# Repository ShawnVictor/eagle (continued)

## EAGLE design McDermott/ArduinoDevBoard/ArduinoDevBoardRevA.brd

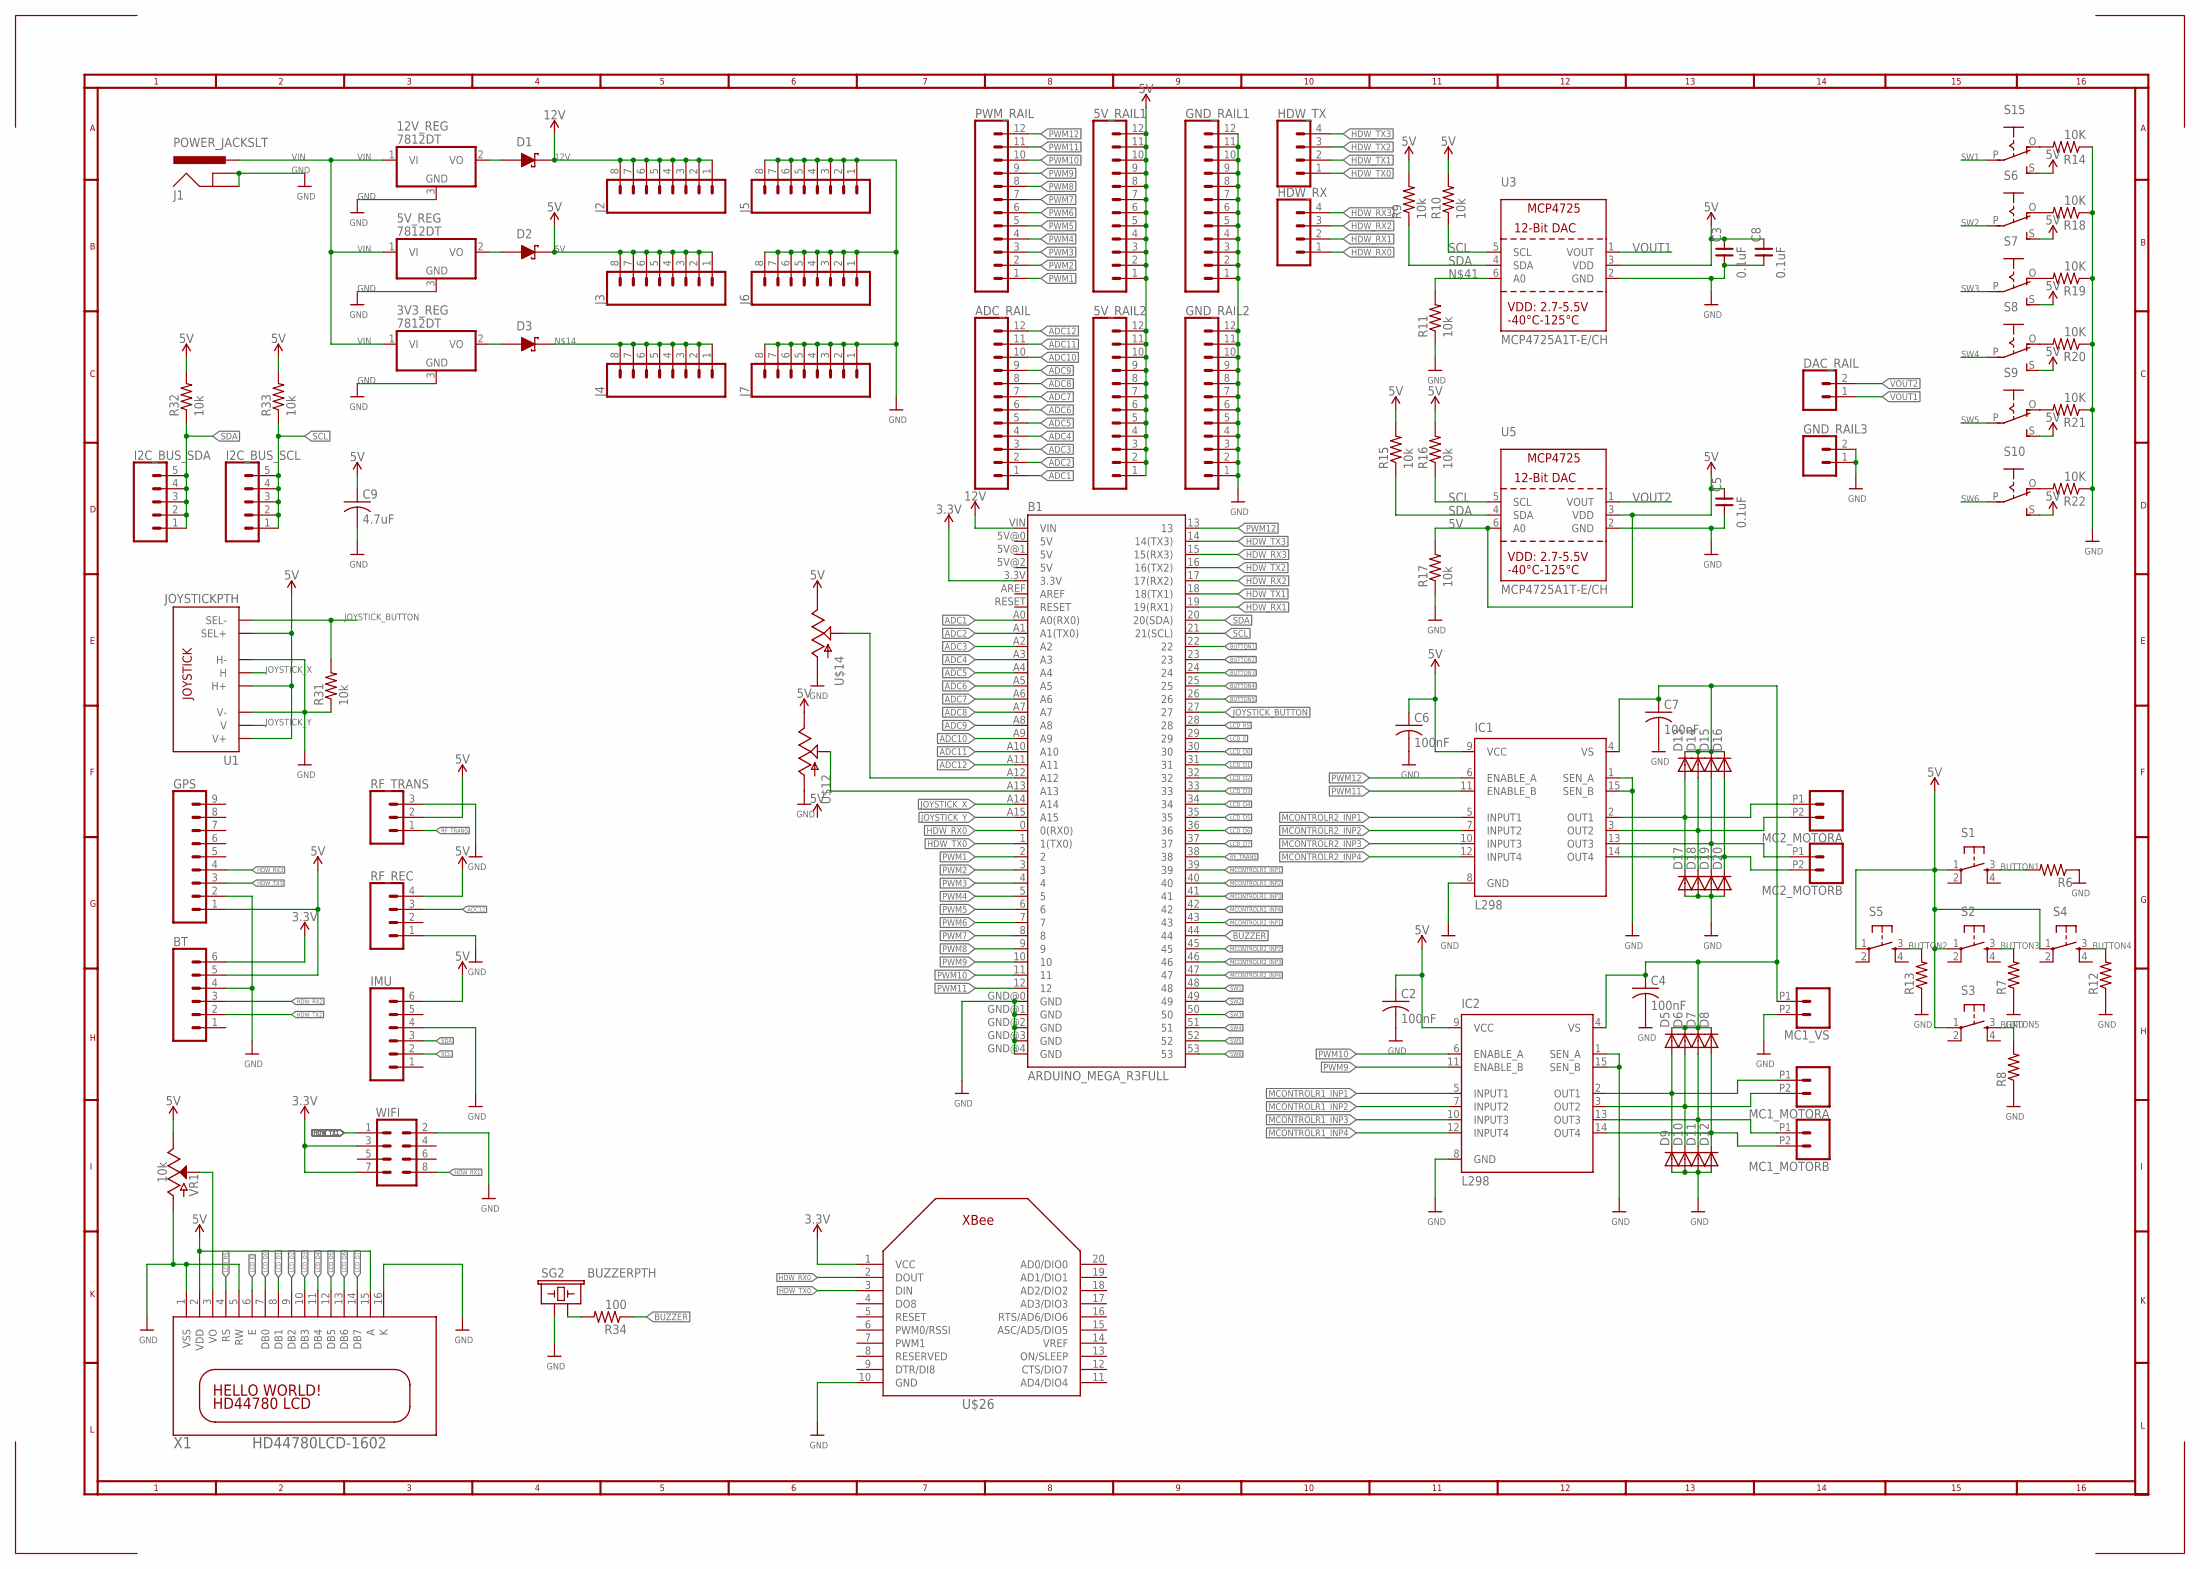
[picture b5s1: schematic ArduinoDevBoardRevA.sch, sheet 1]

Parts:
3V3_REG, 5V_REG, 12V_REG: 7812DT; TO252
5V_RAIL1, 5V_RAIL2: CONN_12; 1X12
ADC_RAIL: CONN_12; 1X12
B1: ARDUINO_MEGA_R3FULL; ARDUINO_MEGA
BT: CONN_06SILK_FEMALE_PTH; 1X06
C2, C4, C6, C7: 100nF; C050-024X044
C3, C5, C8: 0.1uF; 0805
C9: 4.7uF; C050-024X044
D1, D2, D3: D_SCHOTTKYK; SOD-123
D5, D6, D7, D8, D9, D10, D11, D12, D13, D14, D15, D16, D17, D18, D19, D20: DIODE-D-5; D-5
DAC_RAIL: CONN_02; 1X02
GND_RAIL1, GND_RAIL2: CONN_12; 1X12
GND_RAIL3: CONN_02; 1X02
GPS: CONN_09; 1X09
HDW_RX: CONN_04; 1X04
HDW_TX: CONN_04; 1X04
I2C_BUS_SCL, I2C_BUS_SDA: CONN_05; 1X05
IC1, IC2: L298; MULTIWATT-15
IMU: CONN_06SILK_FEMALE_PTH; 1X06
J1: POWER_JACKSLT; POWER_JACK_SLOT
J2, J3, J4, J5, J6, J7: CONN_08"; 1X08
MC1_MOTORA, MC1_MOTORB, MC1_VS, MC2_MOTORA, MC2_MOTORB: CONN_022.54MM_SCREWTERM; 1X02_2.54_SCREWTERM
PWM_RAIL: CONN_12; 1X12
R6, R7, R8, R12, R13: R-US_R0805; R0805
R9, R10, R11, R15, R16, R17, R31, R32, R33: 10k; R0805
R14, R18, R19, R20, R21, R22: 10K; R0805
R34: 100; R0805
RF_REC: CONN_04; 1X04
RF_TRANS: CONN_03; 1X03
S1, S2, S3, S4, S5: TAC_SWITCHSMD; TACTILE_SWITCH_SMD
S6, S7, S8, S9, S10, S15: EG1218S; EG1218
SG2: BUZZERPTH; BUZZER-12MM
U1: JOYSTICKPTH; JOYSTICK
U3, U5: MCP4725A1T-E/CH; SOT23-6
U$12, U$14: POT; ALPS_POT
U$26: XBEE
VR1: 10k; POT-PTH-ALPS-KIT
WIFI: CONN_04X2; 2X4
X1: HD44780LCD-1602; LCD1602

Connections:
3.3V: B1.3.3V, BT.6, U$26.1 (VCC), WIFI.3, WIFI.7
5V: 5V_RAIL1.1, 5V_RAIL1.2, 5V_RAIL1.3, 5V_RAIL1.4, 5V_RAIL1.5, 5V_RAIL1.6, 5V_RAIL1.7, 5V_RAIL1.8, 5V_RAIL1.9, 5V_RAIL1.10, 5V_RAIL1.11, 5V_RAIL1.12, 5V_RAIL2.1, 5V_RAIL2.2, 5V_RAIL2.3, 5V_RAIL2.4, 5V_RAIL2.5, 5V_RAIL2.6, 5V_RAIL2.7, 5V_RAIL2.8, 5V_RAIL2.9, 5V_RAIL2.10, 5V_RAIL2.11, 5V_RAIL2.12, BT.5, C2.1, C3.2, C5.2, C6.1, C8.2, C9.1, D2.2 (C), GPS.1, IC1.9 (VCC), IC2.9 (VCC), IMU.6, J3.1, J3.2, J3.3, J3.4, J3.5, J3.6, J3.7, J3.8, R9.2, R10.2, R15.2, R16.2, R17.2, R32.2, R33.2, RF_REC.4, RF_TRANS.2, S1.1, S2.1, S3.1, S4.1, S5.1, S6.S, S7.S, S8.S, S9.S, S10.S, S15.S, U1.B1A (SEL+), U1.H1 (H+), U1.V1 (V+), U3.3 (VDD), U5.3 (VDD), U5.6 (A0), U$12.P$1 (E), U$14.P$1 (E), VR1.P$1 (E), X1.2 (VDD), X1.15 (A); also elsewhere on the board
12V: B1.VIN, D1.2 (C), J2.1, J2.2, J2.3, J2.4, J2.5, J2.6, J2.7, J2.8
ADC1: ADC_RAIL.1, B1.A0 (A0(RX0)); also elsewhere on the board
ADC2: ADC_RAIL.2, B1.A1 (A1(TX0)); also elsewhere on the board
ADC3: ADC_RAIL.3, B1.A2; also elsewhere on the board
ADC4: ADC_RAIL.4, B1.A3
ADC5: ADC_RAIL.5, B1.A4
ADC6: ADC_RAIL.6, B1.A5
ADC7: ADC_RAIL.7, B1.A6
ADC8: ADC_RAIL.8, B1.A7
ADC9: ADC_RAIL.9, B1.A8
ADC10: ADC_RAIL.10, B1.A9
ADC11: ADC_RAIL.11, B1.A10
ADC12: ADC_RAIL.12, B1.A11, RF_REC.3
BUTTON1: B1.22, R6.2, S1.3
BUTTON2: B1.23, R13.2, S5.3
BUTTON3: B1.24, R7.2, S2.3
BUTTON4: B1.25, R12.2, S4.3
BUTTON5: B1.26, R8.2, S3.3
BUZZER: B1.44, R34.1
GND: 3V3_REG.3 (GND), 5V_REG.3 (GND), 12V_REG.3 (GND), B1.GND@0 (GND), B1.GND@1 (GND), B1.GND@2 (GND), B1.GND@3 (GND), B1.GND@4 (GND), BT.4, C2.2, C3.1, C4.2, C5.1, C6.2, C7.2, C8.1, C9.2, D9.A, D10.A, D11.A, D12.A, D17.A, D18.A, D19.A, D20.A, GND_RAIL1.1, GND_RAIL1.2, GND_RAIL1.3, GND_RAIL1.4, GND_RAIL1.5, GND_RAIL1.6, GND_RAIL1.7, GND_RAIL1.8, GND_RAIL1.9, GND_RAIL1.10, GND_RAIL1.11, GND_RAIL1.12, GND_RAIL2.1, GND_RAIL2.2, GND_RAIL2.3, GND_RAIL2.4, GND_RAIL2.5, GND_RAIL2.6, GND_RAIL2.7, GND_RAIL2.8, GND_RAIL2.9, GND_RAIL2.10, GND_RAIL2.11, GND_RAIL2.12, GND_RAIL3.1, GND_RAIL3.2, GPS.2, IC1.1 (SEN_A), IC1.8 (GND), IC1.15 (SEN_B), IC2.1 (SEN_A), IC2.8 (GND), IC2.15 (SEN_B), IMU.4, J1.GND@1 (GNDBREAK), J1.GND@2 (GND), J5.1, J5.2, J5.3, J5.4, J5.5, J5.6, J5.7, J5.8, J6.1, J6.2, J6.3, J6.4, J6.5, J6.6, J6.7, J6.8, J7.1, J7.2, J7.3, J7.4, J7.5, J7.6, J7.7, J7.8, MC1_VS.P2 (2), R6.1, R7.1, R8.1, R11.1, R12.1, R13.1, R14.1, R17.1, R18.1, R19.1, R20.1, R21.1, R22.1, R31.1, RF_REC.1, RF_TRANS.3, SG2.+ (1), U1.H3 (H-), U1.V3 (V-), U3.2 (GND), U5.2 (GND), U$12.P$3 (A), U$14.P$3 (A), U$26.10 (GND), VR1.P$3 (A), WIFI.2, X1.1 (VSS), X1.5 (RW), X1.16 (K); also elsewhere on the board
HDW_RX0: B1.0 (0(RX0)), HDW_RX.1, U$26.2 (DOUT)
HDW_RX1: B1.19 (19(RX1)), HDW_RX.2, WIFI.8
HDW_RX2: B1.17 (17(RX2)), BT.3, HDW_RX.3
HDW_RX3: B1.15 (15(RX3)), GPS.4, HDW_RX.4
HDW_TX0: B1.1 (1(TX0)), HDW_TX.1, U$26.3 (DIN)
HDW_TX1: B1.18 (18(TX1)), HDW_TX.2, WIFI.1
HDW_TX2: B1.16 (16(TX2)), BT.2, HDW_TX.3
HDW_TX3: B1.14 (14(TX3)), GPS.3, HDW_TX.4
JOYSTICK_BUTTON: B1.27, R31.2, U1.B2A (SEL-)
JOYSTICK_X: B1.A14, U1.H2 (H)
JOYSTICK_Y: B1.A15, U1.V2 (V)
LCD_D0: B1.30, X1.7 (DB0)
LCD_D1: B1.31, X1.8 (DB1)
LCD_D2: B1.32, X1.9 (DB2)
LCD_D3: B1.33, X1.10 (DB3)
LCD_D4: B1.34, X1.11 (DB4)
LCD_D5: B1.35, X1.12 (DB5)
LCD_D6: B1.36, X1.13 (DB6)
LCD_D7: B1.37, X1.14 (DB7)
LCD_E: B1.29, X1.6 (E)
LCD_RS: B1.28, X1.4 (RS)
MCONTROLR1_INP1: B1.39, IC2.5 (INPUT1)
MCONTROLR1_INP2: B1.40, IC2.7 (INPUT2)
MCONTROLR1_INP3: B1.41, IC2.10 (INPUT3)
MCONTROLR1_INP4: B1.42, IC2.12 (INPUT4)
MCONTROLR2_INP1: B1.43, IC1.5 (INPUT1)
MCONTROLR2_INP2: B1.45, IC1.7 (INPUT2)
MCONTROLR2_INP3: B1.46, IC1.10 (INPUT3)
MCONTROLR2_INP4: B1.47, IC1.12 (INPUT4)
unnamed: 12V_REG.2 (VO), D1.1 (A)
unnamed: 5V_REG.2 (VO), D2.1 (A)
unnamed: 3V3_REG.2 (VO), D3.1 (A)
unnamed: C4.1, C7.1, D5.C, D6.C, D7.C, D8.C, D13.C, D14.C, D15.C, D16.C, IC1.4 (VS), IC2.4 (VS), MC1_VS.P1 (1)
unnamed: D3.2 (C), J4.1, J4.2, J4.3, J4.4, J4.5, J4.6, J4.7, J4.8
unnamed: D13.A, D17.C, IC1.2 (OUT1), MC2_MOTORA.P1 (1)
unnamed: D14.A, D18.C, IC1.3 (OUT2), MC2_MOTORA.P2 (2)
unnamed: D15.A, D19.C, IC1.13 (OUT3), MC2_MOTORB.P1 (1)
unnamed: D16.A, D20.C, IC1.14 (OUT4), MC2_MOTORB.P2 (2)
unnamed: B1.A12, U$14.P$2 (S)
unnamed: B1.A13, U$12.P$2 (S)
unnamed: VR1.P$2 (S), X1.3 (VO)
unnamed: R34.2, SG2.- (2)
unnamed: R11.2, U3.6 (A0)
unnamed: D5.A, D9.C, IC2.2 (OUT1), MC1_MOTORA.P1 (1)
unnamed: D6.A, D10.C, IC2.3 (OUT2), MC1_MOTORA.P2 (2)
unnamed: D7.A, D11.C, IC2.13 (OUT3), MC1_MOTORB.P1 (1)
unnamed: D8.A, D12.C, IC2.14 (OUT4), MC1_MOTORB.P2 (2)
unnamed: R14.2, S15.O
unnamed: R18.2, S6.O
unnamed: R19.2, S7.O
unnamed: R20.2, S8.O
unnamed: R21.2, S9.O
unnamed: R22.2, S10.O
PWM1: B1.2, PWM_RAIL.1
PWM2: B1.3, PWM_RAIL.2
PWM3: B1.4, PWM_RAIL.3
PWM4: B1.5, PWM_RAIL.4
PWM5: B1.6, PWM_RAIL.5
PWM6: B1.7, PWM_RAIL.6
PWM7: B1.8, PWM_RAIL.7
PWM8: B1.9, PWM_RAIL.8
PWM9: B1.10, IC2.11 (ENABLE_B), PWM_RAIL.9
PWM10: B1.11, IC2.6 (ENABLE_A), PWM_RAIL.10
PWM11: B1.12, IC1.11 (ENABLE_B), PWM_RAIL.11
PWM12: B1.13, IC1.6 (ENABLE_A), PWM_RAIL.12
RF_TRANS: B1.38, RF_TRANS.1
SCL: B1.21 (21(SCL)), I2C_BUS_SCL.1, I2C_BUS_SCL.2, I2C_BUS_SCL.3, I2C_BUS_SCL.4, I2C_BUS_SCL.5, IMU.2, R10.1, R16.1, R33.1, U3.5 (SCL), U5.5 (SCL); also elsewhere on the board
SDA: B1.20 (20(SDA)), I2C_BUS_SDA.1, I2C_BUS_SDA.2, I2C_BUS_SDA.3, I2C_BUS_SDA.4, I2C_BUS_SDA.5, IMU.3, R9.1, R15.1, R32.1, U3.4 (SDA), U5.4 (SDA); also elsewhere on the board
SW1: B1.48, S15.P
SW2: B1.49, S6.P
SW3: B1.50, S7.P
SW4: B1.51, S8.P
SW5: B1.52, S9.P
SW6: B1.53, S10.P
VIN: 3V3_REG.1 (VI), 5V_REG.1 (VI), 12V_REG.1 (VI), J1.PWR
VOUT1: DAC_RAIL.1, U3.1 (VOUT)
VOUT2: DAC_RAIL.2, U5.1 (VOUT)

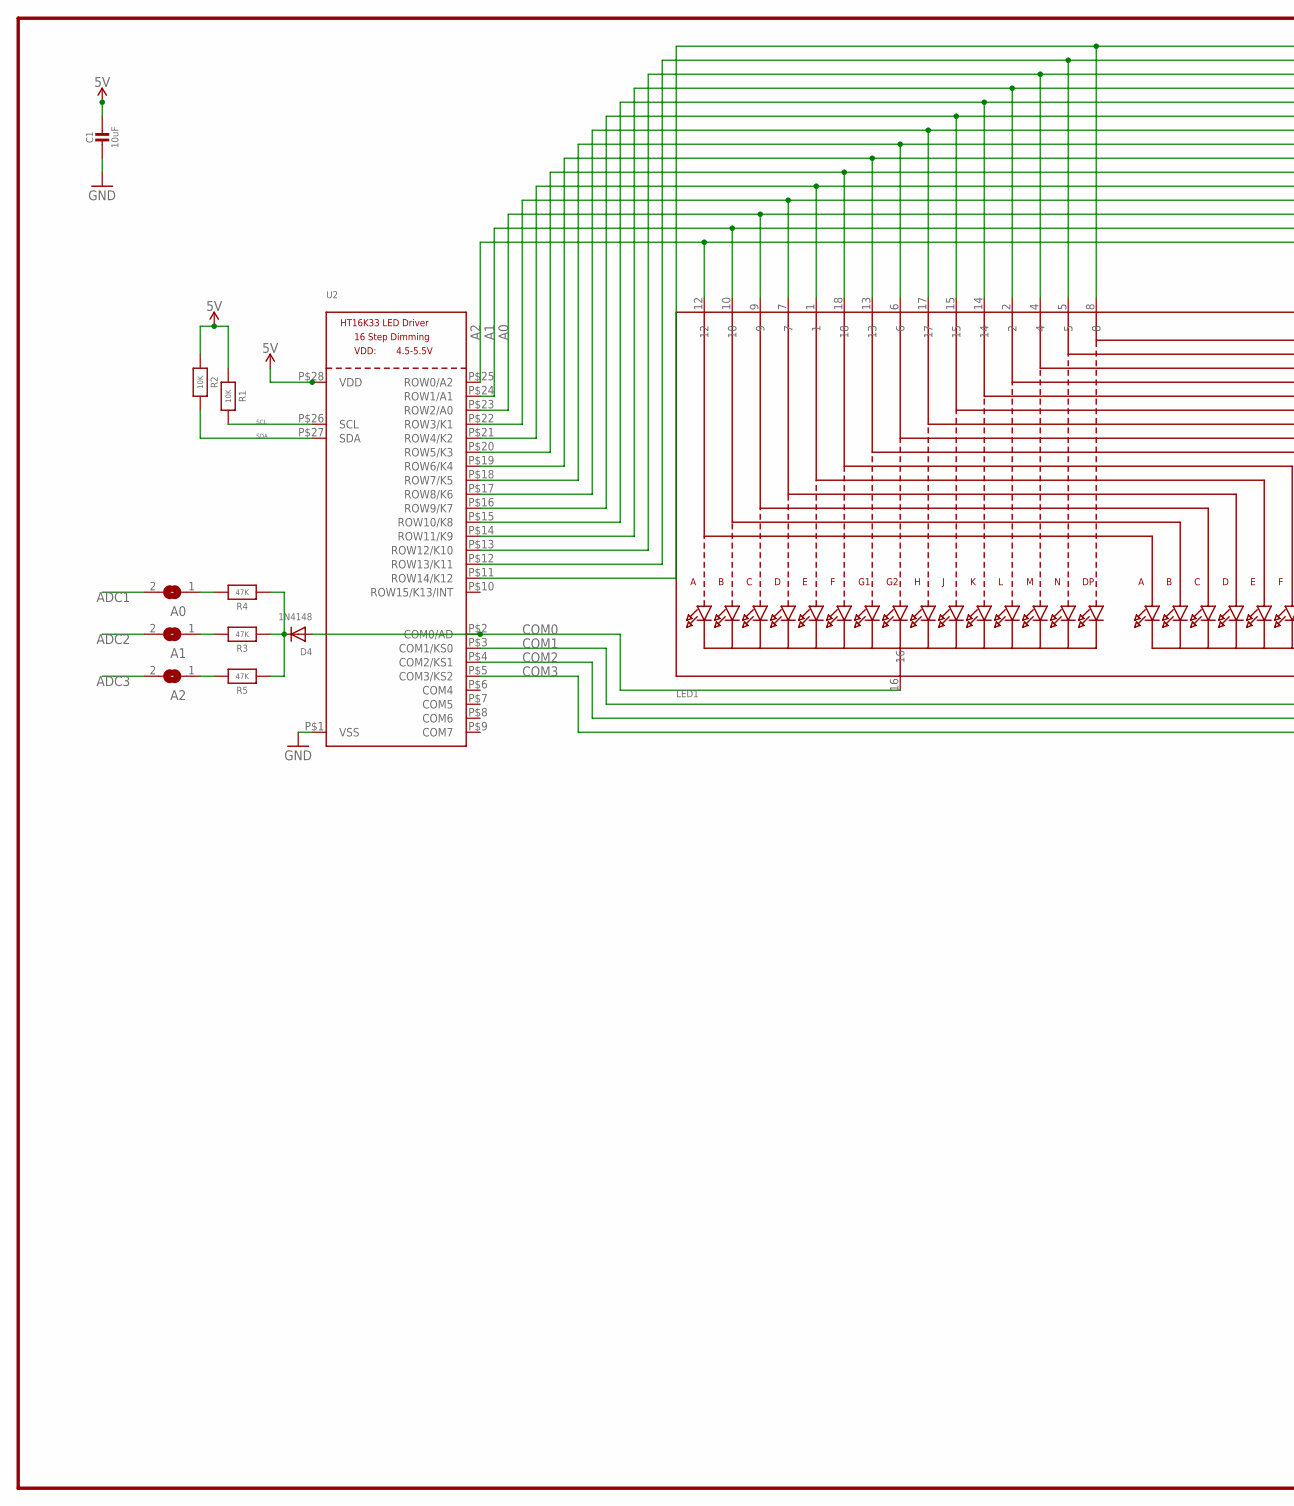
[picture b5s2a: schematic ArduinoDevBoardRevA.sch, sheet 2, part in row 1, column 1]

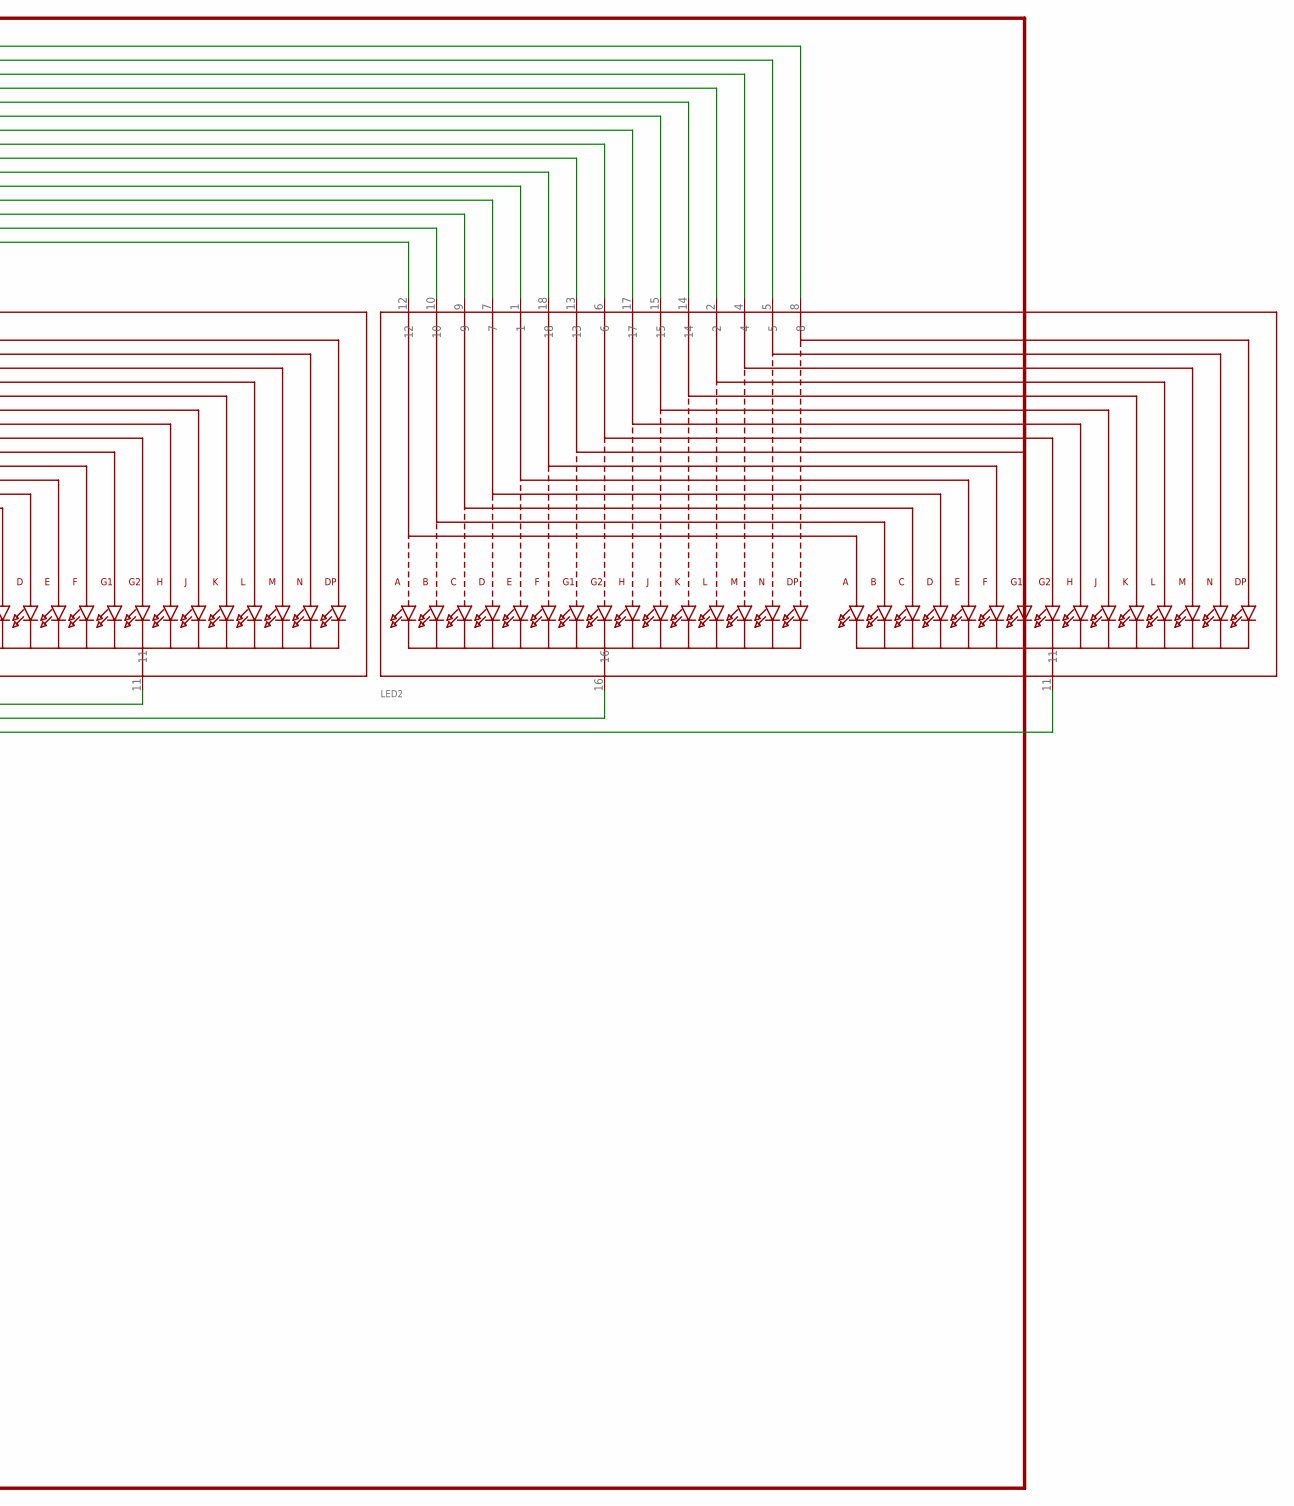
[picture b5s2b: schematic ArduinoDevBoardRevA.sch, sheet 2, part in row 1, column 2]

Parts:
A0, A1, A2: SOLDERJUMPERREFLOW_NOPASTE; SOLDERJUMPER_REFLOW_NOPASTE
C1: 10uF; 0805-NO
D4: 1N4148; SOD-323F
LED1, LED2: DISP_SEGMENT_STARBURST_DUAL_COMMONCATHODE; SEGMENT_STARTBUST_DUAL_KWA-541CBB
R1, R2: 10K; 0805-NO
R3, R4, R5: 47K; 0805-NO
U2: HT16K33_SOP28; SOP28_300MIL

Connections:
5V: R1.1, R2.1, U2.P$28 (VDD); also elsewhere on the board
A0: LED1.9, LED2.9, U2.P$23 (ROW2/A0)
A1: LED1.10, LED2.10, U2.P$24 (ROW1/A1)
A2: LED1.12, LED2.12, U2.P$25 (ROW0/A2)
ADC1: A0.2; also elsewhere on the board
ADC2: A1.2; also elsewhere on the board
ADC3: A2.2; also elsewhere on the board
COM0: D4.A, LED1.16, U2.P$2 (COM0/AD)
COM1: LED1.11, U2.P$3 (COM1/KS0)
COM2: LED2.16, U2.P$4 (COM2/KS1)
COM3: LED2.11, U2.P$5 (COM3/KS2)
GND: C1.2, U2.P$1 (VSS); also elsewhere on the board
unnamed: LED1.7, LED2.7, U2.P$22 (ROW3/K1)
unnamed: LED1.1, LED2.1, U2.P$21 (ROW4/K2)
unnamed: LED1.18, LED2.18, U2.P$20 (ROW5/K3)
unnamed: A1.1, R3.2
unnamed: A0.1, R4.2
unnamed: LED1.13, LED2.13, U2.P$19 (ROW6/K4)
unnamed: LED1.6, LED2.6, U2.P$18 (ROW7/K5)
unnamed: D4.C, R3.1, R4.1, R5.1
unnamed: A2.1, R5.2
unnamed: LED1.17, LED2.17, U2.P$17 (ROW8/K6)
unnamed: LED1.15, LED2.15, U2.P$16 (ROW9/K7)
unnamed: LED1.14, LED2.14, U2.P$15 (ROW10/K8)
unnamed: LED1.2, LED2.2, U2.P$14 (ROW11/K9)
unnamed: LED1.4, LED2.4, U2.P$13 (ROW12/K10)
unnamed: LED1.5, LED2.5, U2.P$12 (ROW13/K11)
unnamed: LED1.8, LED2.8, U2.P$11 (ROW14/K12)
SCL: R1.2, U2.P$26 (SCL); also elsewhere on the board
SDA: R2.2, U2.P$27 (SDA); also elsewhere on the board

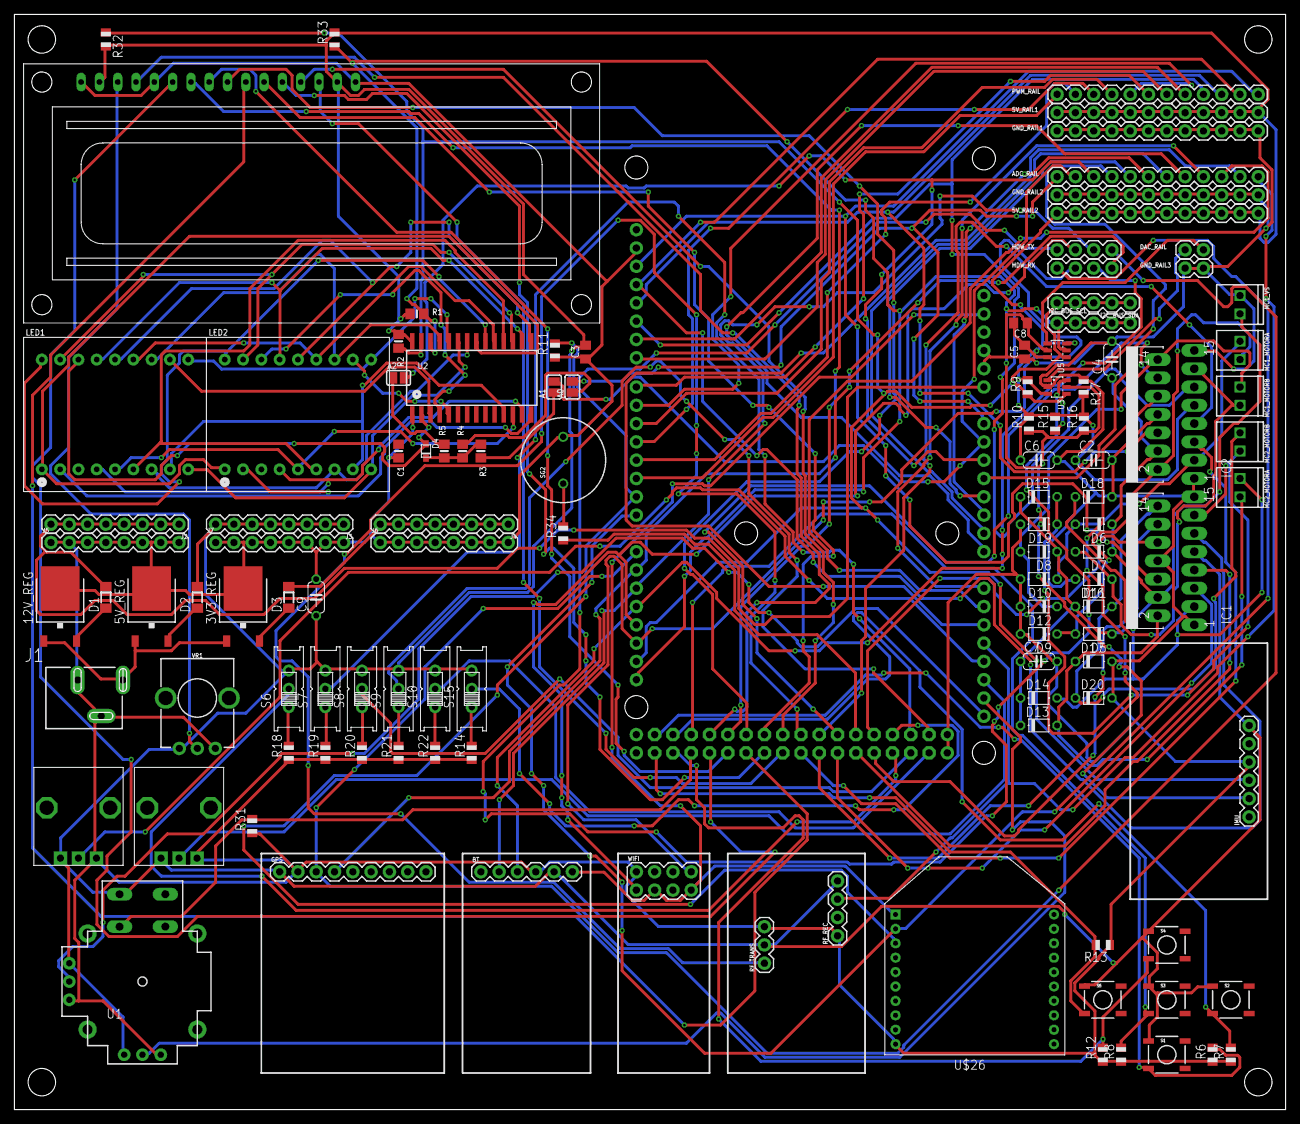
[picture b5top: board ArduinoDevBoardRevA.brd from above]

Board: 2 copper layers, 176.5 x 152.1 mm, 117 parts (1 on the bottom side), 122 nets.

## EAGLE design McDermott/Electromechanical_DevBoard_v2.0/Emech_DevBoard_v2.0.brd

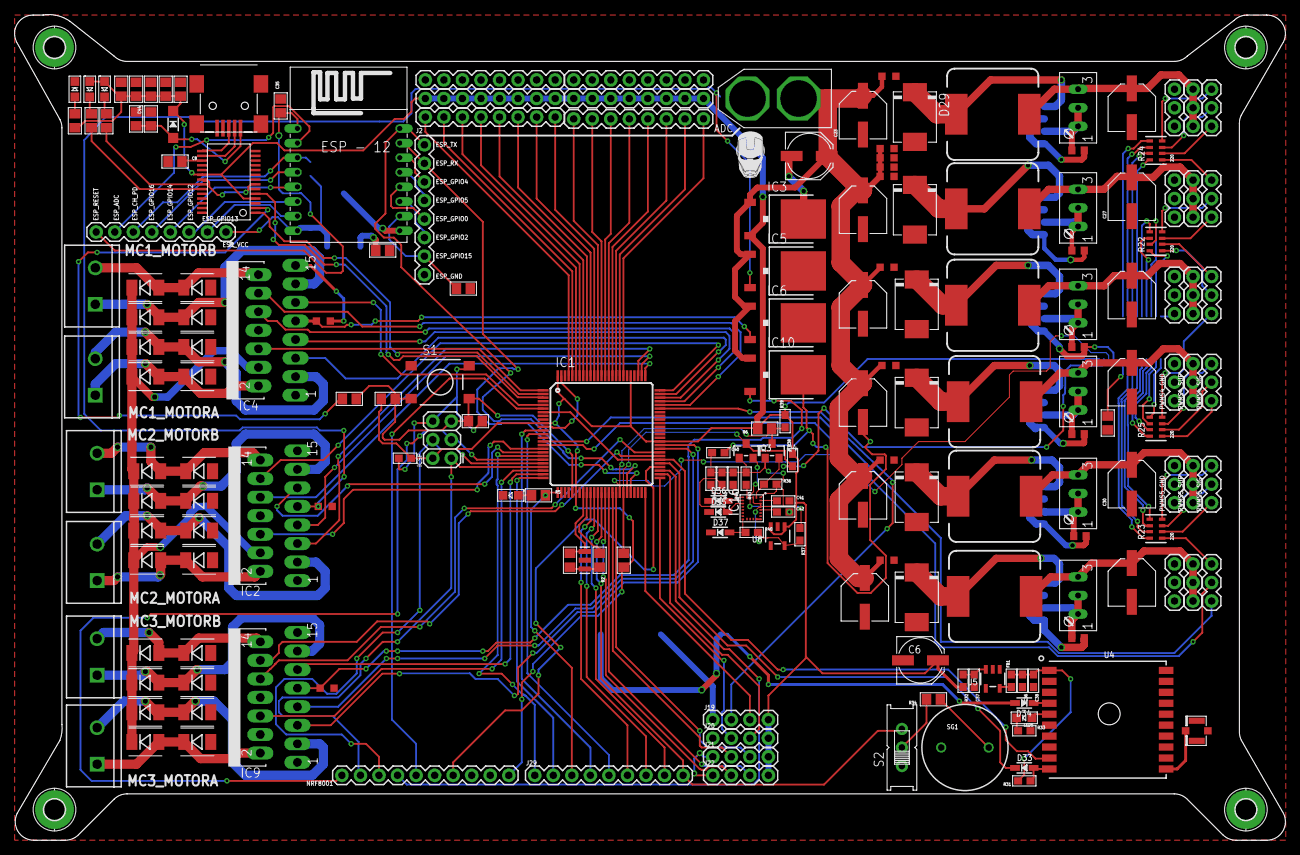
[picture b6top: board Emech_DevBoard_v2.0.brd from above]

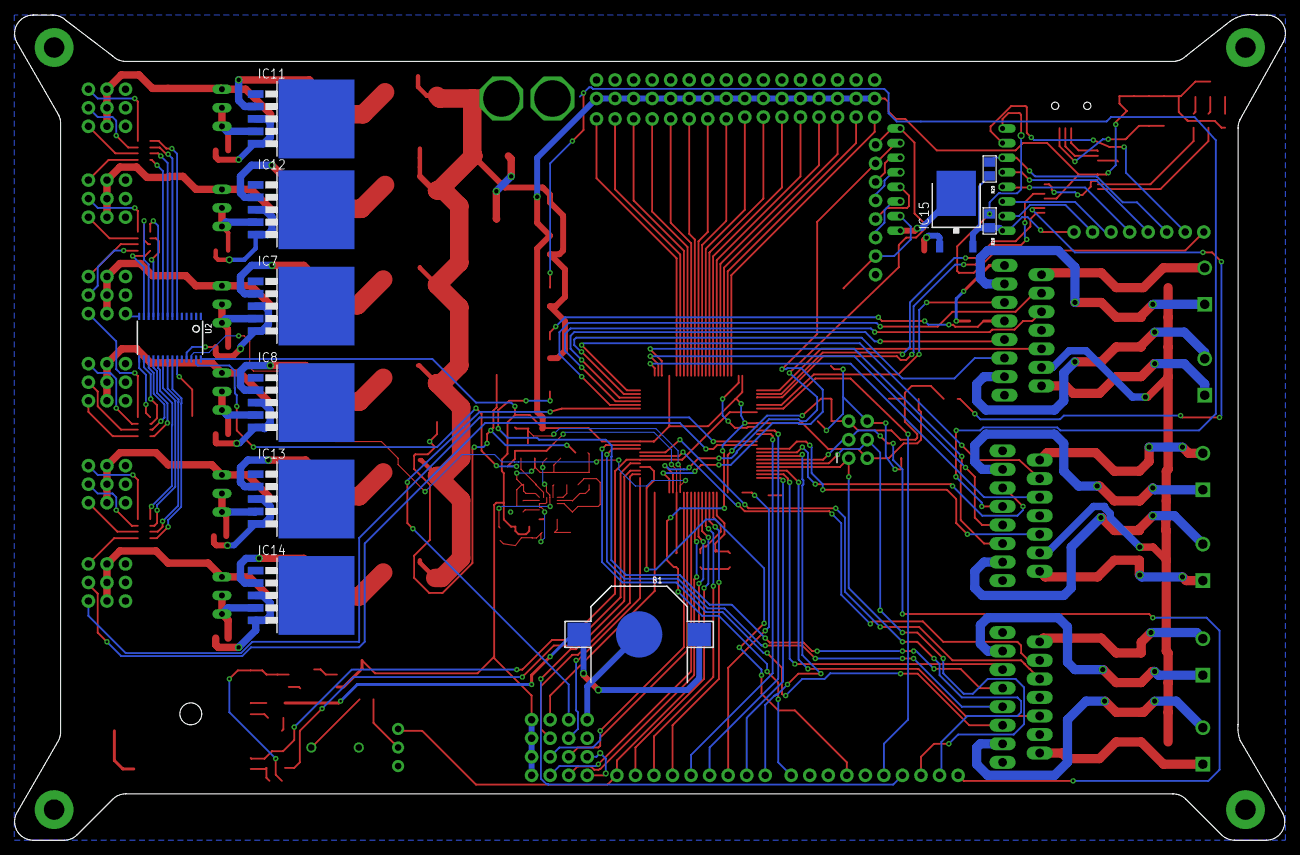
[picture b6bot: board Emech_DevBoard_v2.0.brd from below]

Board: 2 copper layers, 174.1 x 113.1 mm, 210 parts (11 on the bottom side), 185 nets.

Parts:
B1: CR1220
C1, C2, C3, C4, C7, C8, C10, C35, C44: 0.1uF; 0805
C5, C6: 47uF; PANASONIC_D
C9: 4.7uF; 0805
C11, C12, C13, C15, C18, C22: 0.1uF; 0603
C14, C16, C19, C20, C23, C24, C26, C27, C29, C30, C32, C33: 220uF@35V; PANASONIC_D
C17, C21, C25, C28, C31, C34: 100nF; 0603
C36, C37, C39, C40: 10µF; 0603
C38: 0.1µF; 0603
C41: 0.22uF; 0603
C42: 10uF; 0603
C43: 0.33uF; 0805
CN2: USB-MINIB
D2: SOD-123
D3, D4, D5, D6, D7, D8, D9, D10, D11, D12, D13, D14, D15, D16, D17, D18, D21, D22, D23, D24, D25, D26, D27, D28: SS24FSCT-ND; DO-214AA
D19, D20, D29, D30, D31, D32: SS54; DO214AB
D33, D35, D36, D37: 1N4148; SOD-323
D34: CUS520; SOD-323
FB1: 0603
H1, H2, H3, H4: MOUNT-PAD-ROUND2.8; 2,8-PAD
IC1: ATMEGA2560; TQFP100
IC2, IC4, IC9: L298; MULTIWATT-15
IC3: UA78M05; TO252
IC5, IC6, IC10, IC15: 7806DT; TO252
IC7, IC8, IC11, IC12, IC13, IC14: LM2596S; TO263-5
IC16: LSM9DS1; LGA24_3.5X3.1MM
ICSP: FEMALE 2x3; 2X3
J1, J2, J23, J24, J25, J26, J27, J28: 1X08
J19, J20, J21, J22: 1X04
J29: 1X09
L1, L2, L3, L4, L5, L6: SRR1280-330mH; SRR1280
LED1: GREEN; CHIPLED_0805
LED2: YELLOW; CHIPLED_0805
LED3: BLUE; CHIPLED_0805
LED4, LED5: RED; CHIPLED_0805
MC1_MOTORA, MC1_MOTORB, MC2_MOTORA, MC2_MOTORB, MC3_MOTORA, MC3_MOTORB: SCREWTERMINAL-5MM-2
NRF8001: 1X10
PWMS1_GND, PWMS1_SIG, PWMS1_SUP, PWMS2_GND, PWMS2_SIG, PWMS2_SUP, PWMS3_GND, PWMS3_SIG, PWMS3_SUP, PWMS4_GND, PWMS4_SIG, PWMS4_SUP, PWMS5_GND, PWMS5_SIG, PWMS5_SUP, PWMS6_GND, PWMS6_SIG, PWMS6_SUP: 1X03
Q3, Q4: BSS138; SOT23-WIDE
R1: 1m; 0805
R2: 27; 0805
R3, R6, R7, R26, R27, R28: 10k; 0805
R4, R5, R29, R30: 1k; 0805
R8, R9: 680; 0805
R10, R12, R14, R16, R18, R20: 10k; S64W
R11, R13, R15, R17, R19, R21: 330; R0603
R22, R23, R24, R25: 220; RESPACK_4X0603
R31, R32: 10k; 0603
R33: 1k; 0603
R34: 100; 0805
R36, R37, R38, R39, R40, R41, R42, R43, R44: 10K; 0603
S1: DTSM-6
S2: EG1218
SG1: BUZZERPTH; BUZZER-12MM
U1: SSOP28DB
U2: PCA9685; TSSOP28
U3: ESP12
U4: FGPMMOPA6H
U5, U8: MIC5225-3.3; SOT23-5
U$1: RESONATORSMD; RESONATOR-SMD
U$14: XT60
U$55: U.FL

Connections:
3.3V: C8.2, U1.17
ADC0: IC1.97, J25.8
ADC1: IC1.96, J25.7
ADC2: IC1.95, J25.6
ADC3: IC1.94, J25.5
ADC4: IC1.93, J25.4
ADC5: IC1.92, J25.3
ADC6: IC1.91, J25.2
ADC7: IC1.90, J25.1
ADC8: IC1.89, J28.8
ADC9: IC1.88, J28.7
ADC10: IC1.87, J28.6
ADC11: IC1.86, J28.5
ADC12: IC1.85, J28.4
ADC13: IC1.84, J28.3
ADC14: IC1.83, J28.2
ADC15: IC1.82, J28.1
AUX_D1: IC1.38, J29.9, S2.S
AUX_D2: IC1.37, J29.8
AUX_D3: IC1.36, J29.7
AUX_D4: IC1.35, J29.6
AUX_D5: IC1.13, J29.5
AUX_D6: IC1.12, J29.4
AUX_D7: IC1.26, J29.3, R5.2
AUX_D8: IC1.25, J29.2
AUX_D9: IC1.19, J29.1
C2: C41.1, IC16.24
CAP1: C42.1, IC16.21
CS_A/G: D36.A, IC16.7, R41.2
CS_M: D35.A, IC16.8, R42.2
D0/RX0: IC1.2, U1.1
D1/TX0: IC1.3, U1.5
D+: CN2.D+, U1.15
D-: CN2.D-, U1.16
DEN_3V: D37.A, IC16.13, R40.1
ESP_ADC: J1.7, U3.ADC
ESP_CH_PD: J1.6, R29.1, U3.CH_PD
ESP_GPIO0: J2.5, U3.GPIO0
ESP_GPIO2: J2.6, U3.GPIO2
ESP_GPIO4: J2.3, U3.GPIO4
ESP_GPIO5: J2.4, U3.GPIO5
ESP_GPIO12: J1.3, U3.GPIO12
ESP_GPIO13: J1.2, U3.GPIO13
ESP_GPIO14: J1.4, U3.GPIO14
ESP_GPIO15: J2.7, R30.2, U3.GPIO15
ESP_GPIO16: J1.5, U3.GPIO16
ESP_RESET: C35.1, J1.8, R28.1, U3.RESET
ESP_VCC: IC15.2, J1.1, R28.2, R29.2, U3.VCC
FIX: LED5.A, U4.P$5
GND: B1.-, C1.2, C2.2, C3.2, C4.2, C5.-, C6.-, C8.1, C9.1, C10.1, C11.1, C12.1, C13.1, C14.-, C15.1, C16.-, C17.1, C18.1, C19.-, C20.-, C21.1, C22.1, C23.-, C24.-, C25.1, C26.-, C27.-, C28.1, C29.-, C30.-, C31.1, C32.-, C33.-, C34.1, C35.2, C36.2, C37.2, C38.2, C39.2, C40.2, C41.2, C42.2, C43.1, C44.1, CN2.GND, D3.A, D4.A, D5.A, D6.A, D15.A, D16.A, D17.A, D18.A, D19.A, D20.A, D25.A, D26.A, D27.A, D28.A, D29.A, D30.A, D31.A, D32.A, H1.B2,8, H2.B2,8, H3.B2,8, H4.B2,8, IC1.11, IC1.32, IC1.62, IC1.81, IC1.99, IC2.1, IC2.8, IC2.15, IC3.3, IC4.1, IC4.8, IC4.15, IC5.3, IC6.3, IC7.3, IC7.5, IC8.3, IC8.5, IC9.1, IC9.8, IC9.15, IC10.3, IC11.3, IC11.5, IC12.3, IC12.5, IC13.3, IC13.5, IC14.3, IC14.5, IC15.3, IC16.14, IC16.15, IC16.16, IC16.17, IC16.18, IC16.19, IC16.20, ICSP.6, J2.8, J19.1, J20.1, J21.1, J22.1, J24.1, J24.2, J24.3, J24.4, J24.5, J24.6, J24.7, J24.8, J26.1, J26.2, J26.3, J26.4, J26.5, J26.6, J26.7, J26.8, LED1.C, LED2.C, NRF8001.9, PWMS1_GND.1, PWMS1_GND.2, PWMS1_GND.3, PWMS2_GND.1, PWMS2_GND.2, PWMS2_GND.3, PWMS3_GND.1, PWMS3_GND.2, PWMS3_GND.3, PWMS4_GND.1, PWMS4_GND.2, PWMS4_GND.3, PWMS5_GND.1, PWMS5_GND.2, PWMS5_GND.3, PWMS6_GND.1, PWMS6_GND.2, PWMS6_GND.3, R11.1, R13.1, R15.1, R17.1, R19.1, R21.1, R26.2, R27.1, R30.1, R33.2, S1.1, S1.2, SG1.-, U1.7, U1.18, U1.21, U1.25, U2.14, U2.25, U3.GND, U4.P$3, U4.P$8, U4.P$12, U4.P$19, U5.2, U8.2, U$1.2, U$14.-, U$55.P$1, U$55.P$2
GPS_RX: D33.C, IC1.55
GPS_TX: IC1.7, IC1.56, U4.P$9
MCONTROLR1_INP1: IC1.78, IC2.5
MCONTROLR1_INP2: IC1.77, IC2.7
MCONTROLR1_INP3: IC1.76, IC2.10
MCONTROLR1_INP4: IC1.75, IC2.12
MCONTROLR2_INP1: IC1.74, IC4.5
MCONTROLR2_INP2: IC1.73, IC4.7
MCONTROLR2_INP3: IC1.72, IC4.10
MCONTROLR2_INP4: IC1.71, IC4.12
MCONTROLR3_INP1: IC1.60, IC9.5
MCONTROLR3_INP2: IC1.59, IC9.7
MCONTROLR3_INP3: IC1.58, IC9.10
MCONTROLR3_INP4: IC1.57, IC9.12
MISO: IC1.22, ICSP.1, NRF8001.2
MOSI: IC1.21, ICSP.4, NRF8001.3
MOTOR1_PWM_A: IC1.1, IC4.6
MOTOR1_PWM_B: IC1.5, IC4.11
MOTOR2_PWM_A: IC1.17, IC2.6
MOTOR2_PWM_B: IC1.18, IC2.11
MOTOR3_PWM_A: IC1.23, IC9.6
MOTOR3_PWM_B: IC1.24, IC9.11
unnamed: R1.1, R2.2, U$1.3
unnamed: C12.2, IC4.9, IC6.2
unnamed: D19.C, IC7.2, L1.1
unnamed: C15.2, IC2.9, IC5.2
unnamed: LED1.A, R4.1
unnamed: LED2.A, R5.1
unnamed: LED3.C, R8.1
unnamed: R9.2, U1.22
unnamed: R8.2, U1.23
unnamed: LED4.C, R9.1
unnamed: IC7.4, R10.A, R10.S, R11.2
unnamed: C7.1, U1.2
unnamed: D20.C, IC8.2, L2.1
unnamed: D3.C, D10.A, IC4.2, MC1_MOTORA.1
unnamed: D4.C, D9.A, IC4.3, MC1_MOTORA.2
unnamed: D5.C, D8.A, IC4.13, MC1_MOTORB.1
unnamed: D6.C, D7.A, IC4.14, MC1_MOTORB.2
unnamed: IC8.4, R12.A, R12.S, R13.2
unnamed: D21.A, D25.C, IC9.2, MC3_MOTORA.1
unnamed: D22.A, D26.C, IC9.3, MC3_MOTORA.2
unnamed: D23.A, D27.C, IC9.13, MC3_MOTORB.1
unnamed: D24.A, D28.C, IC9.14, MC3_MOTORB.2
unnamed: C18.2, IC9.9, IC10.2
unnamed: D29.C, IC11.2, L3.1
unnamed: IC11.4, R14.A, R14.S, R15.2
unnamed: D30.C, IC12.2, L4.1
unnamed: D11.A, D15.C, IC2.2, MC2_MOTORA.1
unnamed: D12.A, D16.C, IC2.3, MC2_MOTORA.2
unnamed: D13.A, D17.C, IC2.13, MC2_MOTORB.1
unnamed: D14.A, D18.C, IC2.14, MC2_MOTORB.2
unnamed: IC12.4, R16.A, R16.S, R17.2
unnamed: D31.C, IC13.2, L5.1
unnamed: IC13.4, R18.A, R18.S, R19.2
unnamed: D32.C, IC14.2, L6.1
unnamed: IC14.4, R20.A, R20.S, R21.2
unnamed: PWMS1_SIG.3, R24.4
unnamed: PWMS6_SIG.3, R23.1
unnamed: PWMS5_SIG.1, R23.2
unnamed: PWMS5_SIG.2, R23.3
unnamed: PWMS5_SIG.3, R23.4
unnamed: PWMS4_SIG.1, R25.1
unnamed: PWMS4_SIG.2, R25.2
unnamed: PWMS4_SIG.3, R25.3
unnamed: PWMS3_SIG.1, R25.4
unnamed: PWMS3_SIG.2, R22.1
unnamed: PWMS3_SIG.3, R22.2
unnamed: PWMS2_SIG.1, R22.3
unnamed: PWMS2_SIG.2, R22.4
unnamed: PWMS2_SIG.3, R24.1
unnamed: PWMS1_SIG.2, R24.3
unnamed: PWMS1_SIG.1, R24.2
unnamed: U4.P$11, U$55.P$3
unnamed: D33.A, R31.1, U4.P$10
unnamed: C36.1, C38.1, FB1.2, R31.2, U4.P$1
unnamed: C37.1, R32.1, U5.3
unnamed: LED5.C, R33.1
unnamed: B1.+$1, B1.+$2, D34.A
unnamed: R34.2, S2.P
unnamed: R34.1, SG1.+
NRF_RDY: IC1.6, NRF8001.5
NRF_REQ: IC1.53, NRF8001.4
NRF_RST: IC1.54, NRF8001.7
OE: R26.1, U2.23
OUT: FB1.1, U5.5
PWM0: R24.5, U2.6
PWM1: R24.6, U2.7
PWM2: R24.7, U2.8
PWM3: R24.8, U2.9
PWM4: R22.5, U2.10
PWM5: R22.6, U2.11
PWM6: R22.7, U2.12
PWM7: R22.8, U2.13
PWM8: R25.5, U2.15
PWM9: R25.6, U2.16
PWM10: R25.7, U2.17
PWM11: R25.8, U2.18
PWM12: R23.5, U2.19
PWM13: R23.6, U2.20
PWM14: R23.7, U2.21
PWM15: R23.8, U2.22
PWM16: IC1.16, PWMS6_SIG.2
PWM17: IC1.15, PWMS6_SIG.1
RESET: C4.1, C7.2, IC1.30, ICSP.5, R3.1, S1.3, S1.4
SCK: IC1.20, ICSP.3, NRF8001.1
SCL: IC1.43, Q4.3, R6.1, R39.1, U2.26
SCL_3V: IC16.2, Q4.2, R36.1
SDA: IC1.44, Q3.3, R7.1, R38.1, U2.27
SDA_3V: IC16.4, Q3.2, R37.1
SDO_AG: IC16.5, R43.2
SDO_M: IC16.6, R44.2
SW_MODE_SUPPLY1: C24.+, L3.2, PWMS1_SUP.1, PWMS1_SUP.2, PWMS1_SUP.3, R14.E
SW_MODE_SUPPLY2: C27.+, L4.2, PWMS2_SUP.1, PWMS2_SUP.2, PWMS2_SUP.3, R16.E
SW_MODE_SUPPLY3: C16.+, L1.2, PWMS3_SUP.1, PWMS3_SUP.2, PWMS3_SUP.3, R10.E
SW_MODE_SUPPLY4: C20.+, L2.2, PWMS4_SUP.1, PWMS4_SUP.2, PWMS4_SUP.3, R12.E
SW_MODE_SUPPLY5: C30.+, L5.2, PWMS5_SUP.1, PWMS5_SUP.2, PWMS5_SUP.3, R18.E
SW_MODE_SUPPLY6: C33.+, L6.2, PWMS6_SUP.1, PWMS6_SUP.2, PWMS6_SUP.3, R20.E
UC_5V: C1.1, C2.1, C3.1, C6.+, C39.1, C44.2, D2.C, IC1.10, IC1.31, IC1.61, IC1.80, IC1.100, IC3.2, ICSP.2, J19.4, J20.4, J21.4, J22.4, J23.1, J23.2, J23.3, J23.4, J23.5, J23.6, J23.7, J23.8, J27.1, J27.2, J27.3, J27.4, J27.5, J27.6, J27.7, J27.8, LED3.A, LED4.A, NRF8001.10, R3.2, R4.2, R6.2, R7.2, R27.2, R32.2, R38.2, R39.2, U1.4, U1.20, U2.28, U8.1, U8.3
US1_D1: IC1.50, J19.3
US1_D2: IC1.70, J19.2
US2_D1: IC1.52, J20.3
US2_D2: IC1.51, J20.2
US3_D1: IC1.42, J21.3
US3_D2: IC1.41, J21.2
US4_D1: IC1.40, J22.3
US4_D2: IC1.39, J22.2
VBACKUP: D34.C, U4.P$4
VDD: C40.1, IC16.1, IC16.3, IC16.22, IC16.23, Q3.1, Q4.1, R36.2, R37.2, R40.2, R41.1, R42.1, R43.1, R44.1, U8.5
VIN: C5.+, C11.2, C13.2, C14.+, C17.2, C19.+, C21.2, C22.2, C23.+, C25.2, C26.+, C28.2, C29.+, C31.2, C32.+, C34.2, C43.2, D7.C, D8.C, D9.C, D10.C, D11.C, D12.C, D13.C, D14.C, D21.C, D22.C, D23.C, D24.C, IC2.4, IC3.1, IC4.4, IC5.1, IC6.1, IC7.1, IC8.1, IC9.4, IC10.1, IC11.1, IC12.1, IC13.1, IC14.1, IC15.1, U$14.+
VUSB: C9.2, C10.2, CN2.VBUS, D2.A
WIFI_RX: IC1.46, J2.2, U3.RX
WIFI_TX: IC1.45, J2.1, U3.TX
XTAL1: IC1.34, R2.1
XTAL2: IC1.33, R1.2, U$1.1
